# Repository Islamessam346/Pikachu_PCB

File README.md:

# Pikachu_PCB

Ever wondered how a pikachu made with LEDs look like? this is a PCB that lights a set of lamps, where the design is inspired by the cute pokemon mascot, Pikachu!

## Schematic

## PCB

## Features
- a nice light decoration for your room
- the very cute pokemon pikachu
- a lot of lightning bolts+the hack club flag
- Turnable on and off

## How to build
Just order the PCB & components, open up the KiCAD file and build it accordingly.

## BOM
- 1 	Battery holder
- 6   2.12V LED
- 6 	10k Resistor
- 1 	Button switch

Made by `@Eslam Essam` on slack id :U08260E7B4J

Made as a part of http://solder.hackclub.com/!

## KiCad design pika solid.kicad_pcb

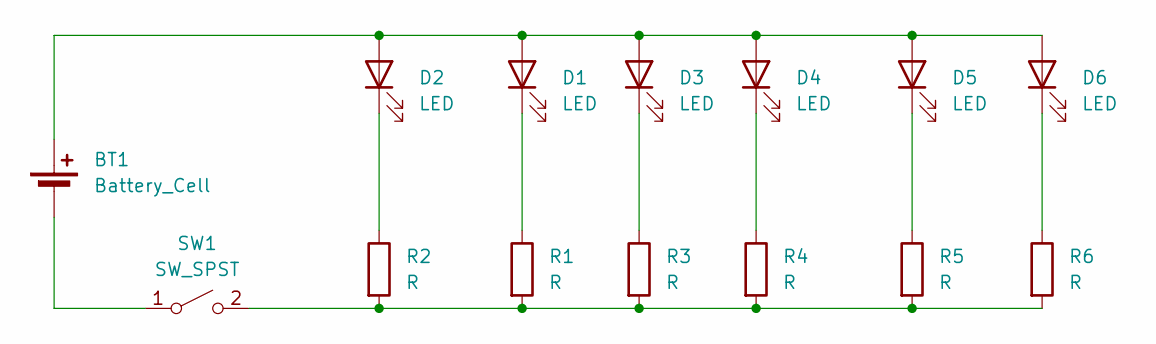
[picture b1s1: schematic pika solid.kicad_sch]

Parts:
BT1: Battery_Cell; BatteryHolder_Keystone_3034_1x20mm
D1, D2, D3, D4, D5, D6: LED; LED_D5.0mm
R1, R2, R3, R4, R5, R6: R; R_Axial_DIN0207_L6.3mm_D2.5mm_P7.62mm_Horizontal
SW1: SW_SPST; SW_SPST_Omron_B3F-40xx

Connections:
unnamed: BT1.1 (+), D1.2 (A), D2.2 (A), D3.2 (A), D4.2 (A), D5.2 (A), D6.2 (A)
unnamed: BT1.2 (-), SW1.1 (A)
unnamed: D1.1 (K), R1.1
unnamed: D2.1 (K), R2.1
unnamed: D3.1 (K), R3.1
unnamed: D4.1 (K), R4.1
unnamed: D5.1 (K), R5.1
unnamed: D6.1 (K), R6.1
unnamed: R1.2, R2.2, R3.2, R4.2, R5.2, R6.2, SW1.2 (B)

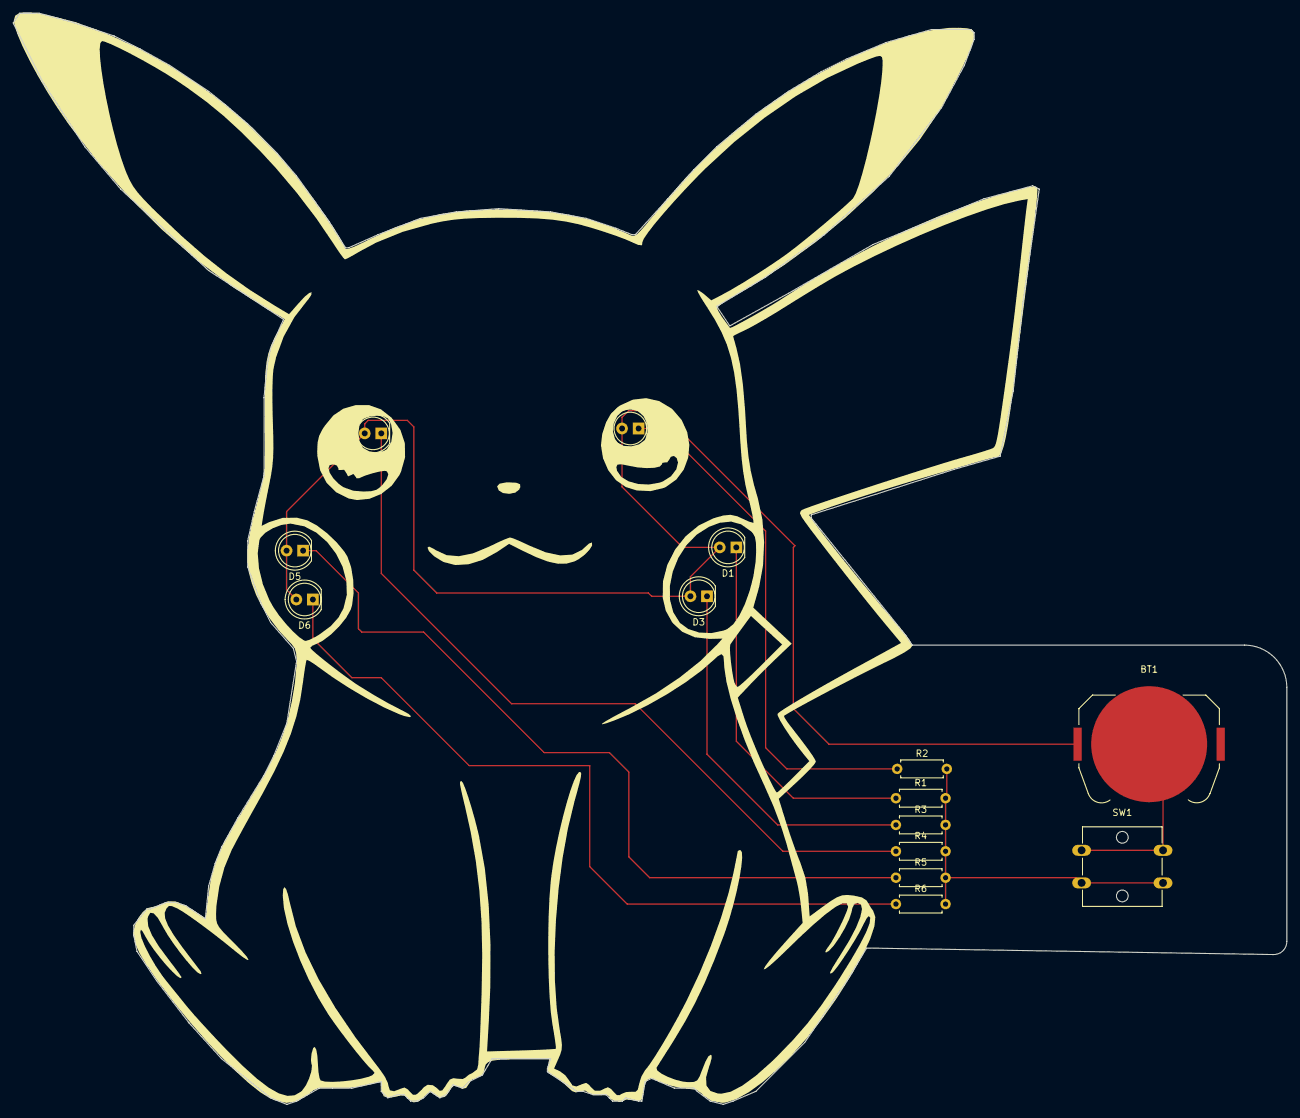
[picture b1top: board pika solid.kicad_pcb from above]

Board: 2 copper layers, 195.5 x 167.5 mm, 14 parts (0 on the bottom side), 9 nets.

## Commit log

2025-05-28 README.md
